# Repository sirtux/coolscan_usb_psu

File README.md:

# Coolscan PSU Replacement
This is my take on an replacement PSU for the Coolscan 35mm Scanner (LS-40, 4000, 5000, et al),
as my PSU broke and replacements are no longer available.

This PCB is not cost optimized at all, but for those scanners it simply doesn't matter..

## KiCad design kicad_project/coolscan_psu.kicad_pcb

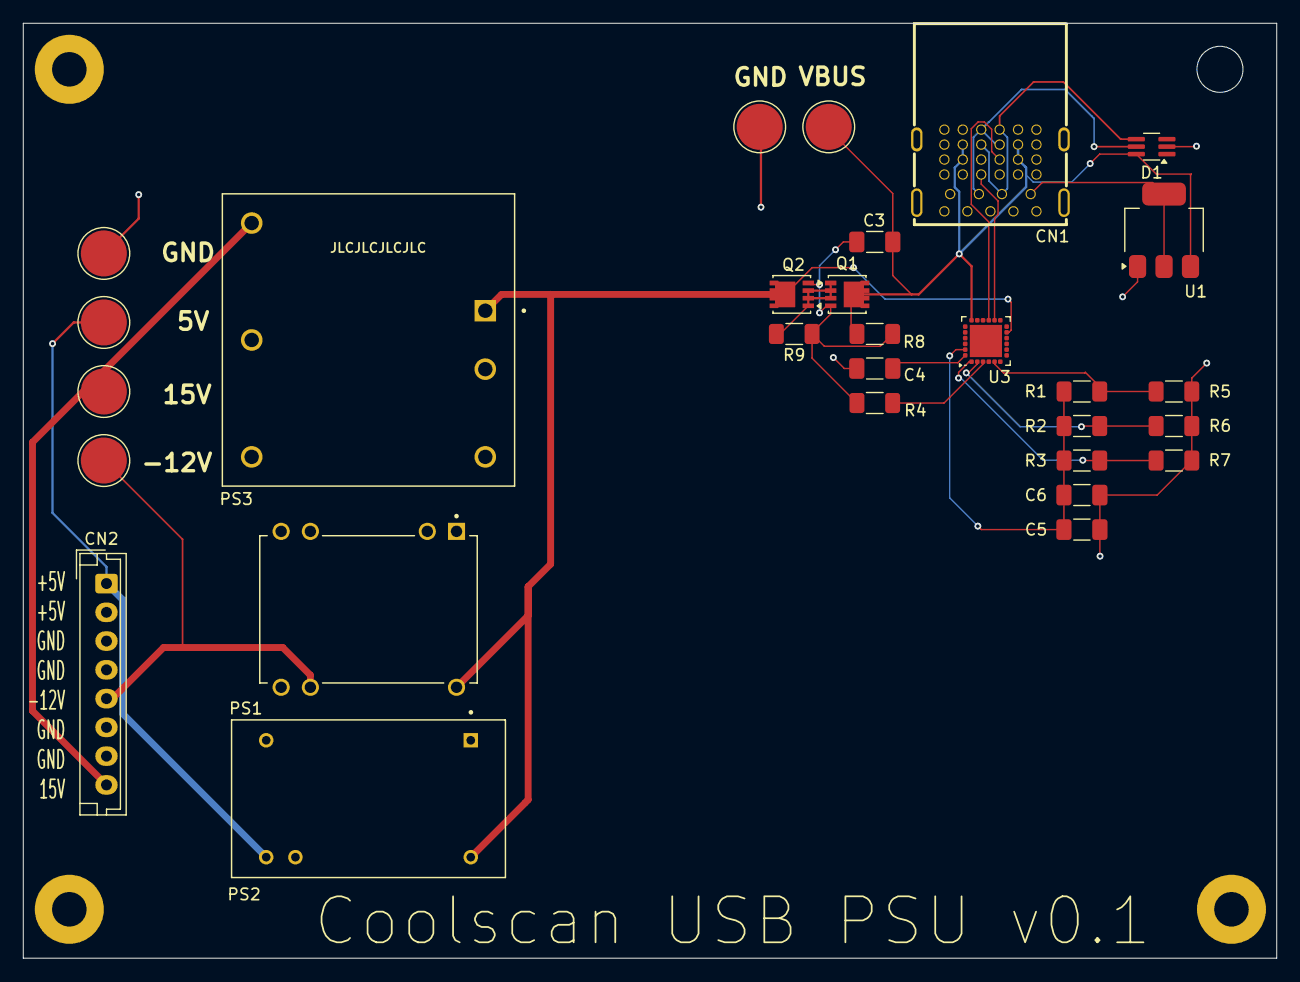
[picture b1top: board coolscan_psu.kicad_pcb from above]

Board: 4 copper layers, 108.9 x 81.2 mm, 33 parts (0 on the bottom side), 20 nets.

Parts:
C3, C4, C5: 1uF 50V 1206 RoHS; C_1206_3216Metric_Pad1.33x1.80mm_HandSolder
C6: 100nF 50V 1206 RoHS; C_1206_3216Metric_Pad1.33x1.80mm_HandSolder
CN1: GT-USB-7106A; USB-C-TH_GT-USB-7106A
CN2: Power Out; JST_EH_B8B-EH-A_1x08_P2.50mm_Vertical
D1: SMF05CT1G; SOT-363_SC-70-6_Handsoldering
H1, H2, H3: MountingHole; MountingHole_3mm_Pad
H4: MountingHole; MountingHole_4mm
PS1: TDR_2-1212 (12V); TDR2-1211
PS2: TEL_15-1211N (5V); TEL15-1211N
PS3: THL_25-1213 (15V); THL25-1213
Q1, Q2: DMP3013SFV-7; Vishay_PowerPAK_1212-8_Single
R1, R2, R3, R6: 5.1k 1206; R_1206_3216Metric_Pad1.30x1.75mm_HandSolder
R4: 1KOhms ±1% 1/4W 1206 RoHS; R_1206_3216Metric_Pad1.30x1.75mm_HandSolder
R5: 10k 1206; R_1206_3216Metric_Pad1.30x1.75mm_HandSolder
R7: 2.4k 1206; R_1206_3216Metric_Pad1.30x1.75mm_HandSolder
R8: 10KOhms 1206; R_1206_3216Metric_Pad1.30x1.75mm_HandSolder
R9: 47KOhms ±1% 1/8W 0805 RoHS; R_1206_3216Metric_Pad1.30x1.75mm_HandSolder
TP1, TP2, TP3, TP4, TP5, TP6: TestPoint; TestPoint_Pad_D4.0mm
U1: NCP1117-5.0_SOT223; SOT-223-3_TabPin2
U3: CYPD3177-24LQXQ; TQFN-24-1EP_4x4mm_P0.5mm_EP2.8x2.8mm_PullBack

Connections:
+5V: CN2.1, CN2.2, PS2.9 (+VOUT), TP2.1
+15V: CN2.8, PS3.3 (+VOUT), TP3.1
+USBVOLTAGE: PS1.14 (+VIN(VCC)), PS2.16 (+VIN), PS3.1 (+VIN(VCC)), Q2.5 (D), U3.11 (VDC_OUT)
-12V: CN2.5, PS1.9 (-VOUT), TP4.1
/USB PD Controller/CC1: CN1.A5 (CC1), U3.15 (CC1)
/USB PD Controller/CC2: CN1.B5 (CC2), U3.14 (CC2)
/USB PD Controller/ISNK_COARSE: R1.2, R5.1, U3.5 (ISNK_COARSE)
/USB PD Controller/VBUS: C3.1, CN1.A4 (VBUS), CN1.A9 (VBUS), CN1.B4 (VBUS), CN1.B9 (VBUS), D1.6, Q1.5 (D), R8.1, TP5.1, U1.3 (VI), U3.18 (VBUS_IN)
/USB PD Controller/VBUS_FET_EN: C3.2, Q1.4 (G), Q2.4 (G), R4.1, R8.2, R9.1
/USB PD Controller/VBUS_MAX: R2.2, R6.1, U3.2 (VBUS_MAX)
/USB PD Controller/VBUS_MIN: R3.2, R7.1, U3.1 (VBUS_MIN)
/USB PD Controller/VDDD: C5.2, C6.1, R1.1, R2.1, R3.1, U3.23 (VDDD)
/USB Socket/USB+: CN1.3 (D+_A), CN1.A6 (D+), CN1.B6 (D+), D1.5
/USB Socket/USB-: CN1.2 (D-_A), CN1.A7 (D-), CN1.B7 (D-), D1.4
/USB Socket/USB_A_VBUS: CN1.1 (VBUS_A), U1.2 (VO)
GND: C4.1, C5.1, C6.2, CN1.4 (GND_A), CN1.7 (GND_DRAIN), CN1.A1 (GND), CN1.A12 (GND), CN1.B1 (GND), CN1.B12 (GND), D1.2, PS1.1 (-VIN(GND)), PS2.1 (-VIN), PS3.2 (-VIN(GND)), R5.2, R6.2, R7.2, TP6.1, U1.1 (GND), U3.6 (ISNK_FINE), U3.19 (GND), U3.22 (GND), U3.25 (EP)
GND1: CN2.3, CN2.4, CN2.6, CN2.7, PS1.8 (+VOUT), PS2.10 (-VOUT), PS3.5 (-VOUT), TP1.1
unnamed: Q1.1 (S), Q1.2 (S), Q1.3 (S), Q2.1 (S), Q2.2 (S), Q2.3 (S), R9.2
unnamed: R4.2, U3.3 (VBUS_FET_EN)
unnamed: C4.2, U3.24 (VCCD)

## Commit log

2024-11-15 Added gitignore
2024-11-16 More ignores
